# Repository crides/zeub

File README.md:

# Zeub

zeub is meant to be a pixel clock and a IoT hub. The name comes from a smooshed version of zeit (German for time) and hub.

It currently has:
- a 8x8 RGB LED matrix and a 32x8 white LED matrix
- 2 2-channel LED strip controllers (for controlling LED strips with warm and cool white lights in my room)
- a 128x64 OLED screen
- a TMP117 precision temperature sensor
- 2 front facing speakers, using 2 MAX98357 DACs
- a DS3212 battery backed RTC
- a EVQWGD001 rotary encoder, and a 5-way joystick
- a nRF52840 microcontroller, which supports USB, BLE and 802.15.4 (ZigBee etc.) protocols

Version 2 assembled displaying a clock icon and time (the right side is green because uh.. I messed up the PCBA parts assignment): 

The current firmware fetches the current time (once; supports connection at 2 times for drift correction) from a CTS (Current Time Service) from a BLE connection. This is currently done using my phone through the nRF Connect app. The time is then displayed on both the LED matrix (along with a clock icon), and the OLED along with the date and current temperature. It also sets the brightness of one LED strip using a preconfigured (but can be reconfigured through BLE) schedule. The other LED strip (which is actually my desk light) is controlled by the scroll wheel. It also streams audio from the USB to the speakers, for testing of the audio interface.

The hub part of the project still doesn't really exist yet, as I haven't had time to get to it.

Version 1 has basically the same features, but also included 2 microphones for testing. However the LED matrix did not work properly as I used 2 LED matrix controllers together in the same matrix.

The LED strips were also connected through a TRRS cable but without an actual connector, as I flipped the control polarity of the LED strips (they are common anode instead of common cathode).

Case iterations for v1 (the cone in the back is for better airflow to the temperature sensor, for more accurate reading of the environment):

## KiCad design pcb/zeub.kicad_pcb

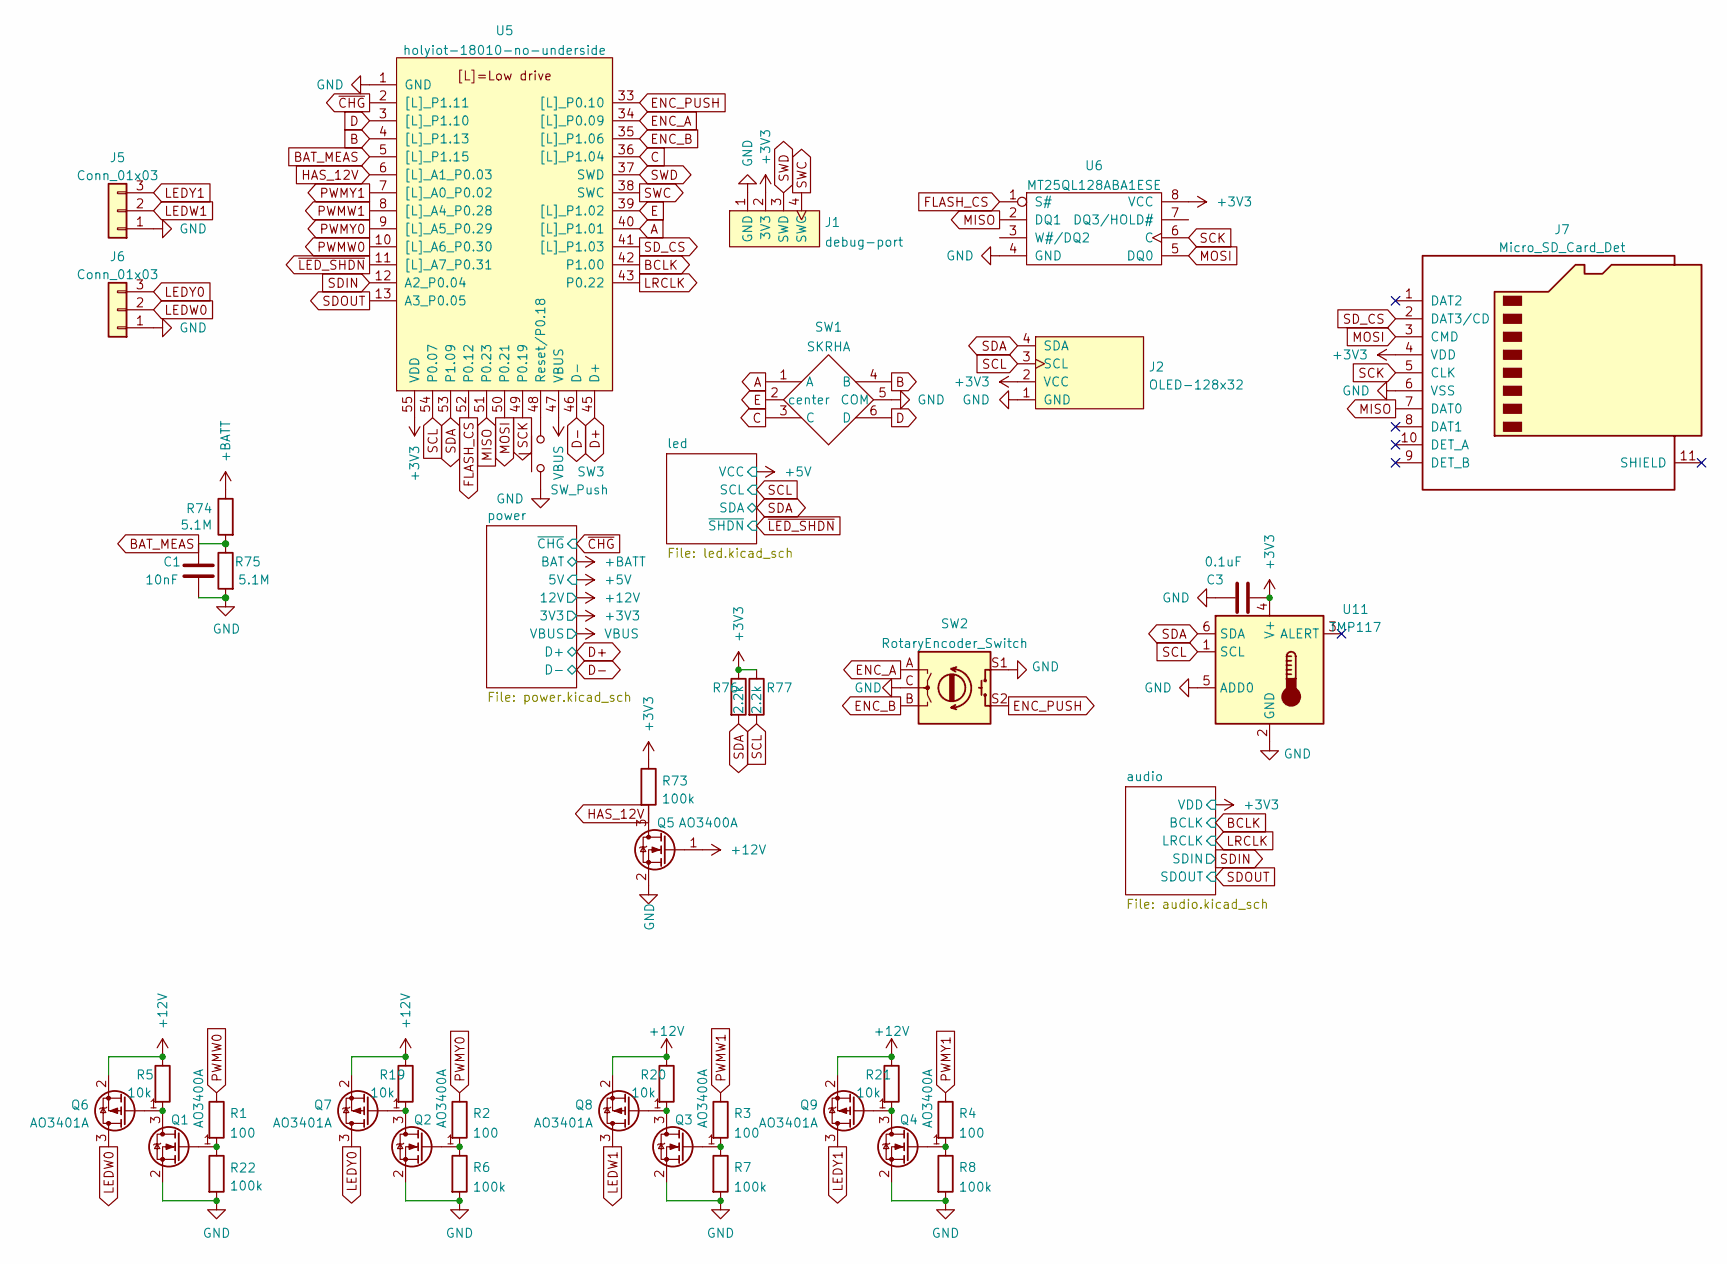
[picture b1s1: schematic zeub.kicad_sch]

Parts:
C1: 10nF; C_0603_1608Metric
C3: 0.1uF; C_0603_1608Metric
J1: debug-port; debug-port-single-side
J2: OLED-128x32; OLED-128x64
J5, J6: Conn_01x03; PinHeader_1x03_P2.54mm_Vertical
J7: Micro_SD_Card_Det; molex-503182-1852
Q1, Q2, Q3, Q4, Q5: AO3400A; SOT-23
Q6, Q7, Q8, Q9: AO3401A; SOT-23
R1, R2, R3, R4: 100; R_0603_1608Metric
R5, R19, R20, R21: 10k; R_0603_1608Metric
R6, R7, R8, R22, R73: 100k; R_0603_1608Metric
R74, R75: 5.1M; R_0603_1608Metric
R76, R77: 2.2k; R_0603_1608Metric
SW1: SKRHA; SKRHA-boss
SW2: RotaryEncoder_Switch; EVQWGD001
SW3: SW_Push; SW_SPST_B3U-1000P
U5: holyiot-18010-no-underside
U6: MT25QL128ABA1ESE; SOIC-8_5.23x5.23mm_P1.27mm
U11: TMP117; WSON-6-1EP_2x2mm_P0.65mm_EP1x1.6mm

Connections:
+3V3: C3.2, J1.2 (3V3), J2.2 (VCC), J7.4 (VDD), R73.1, R76.1, R77.1, U5.55 (VDD), U6.8 (VCC), U11.4 (V+); also elsewhere on the board
+12V: Q5.1 (G), Q6.2 (S), Q7.2 (S), Q8.2 (S), Q9.2 (S), R5.1, R19.1, R20.1, R21.1; also elsewhere on the board
+BATT: R74.1; also elsewhere on the board
A: SW1.1 (A), U5.40 ([L]_P1.01)
B: SW1.4 (B), U5.4 ([L]_P1.13)
BAT_MEAS: C1.1, R74.2, R75.1, U5.5 ([L]_P1.15)
BCLK: U5.42 (P1.00); also elsewhere on the board
C: SW1.3 (C), U5.36 ([L]_P1.04)
D: SW1.6 (D), U5.3 ([L]_P1.10)
D+: U5.45 (D+); also elsewhere on the board
D-: U5.46 (D-); also elsewhere on the board
E: SW1.2 (center), U5.39 ([L]_P1.02)
ENC_A: SW2.A, U5.34 ([L]_P0.09)
ENC_B: SW2.B, U5.35 ([L]_P1.06)
ENC_PUSH: SW2.S2, U5.33 ([L]_P0.10)
FLASH_CS: U5.52 (P0.12), U6.1 (S#)
GND: C1.2, C3.1, J1.1 (GND), J2.1 (GND), J5.1, J6.1, J7.6 (VSS), Q1.2 (S), Q2.2 (S), Q3.2 (S), Q4.2 (S), Q5.2 (S), R6.2, R7.2, R8.2, R22.2, R75.2, SW1.5 (COM), SW2.C, SW2.S1, SW3.1, U5.1 (GND), U5.32 (GND), U5.44 (GND), U6.4 (GND), U11.2 (GND), U11.5 (ADD0), U11.7 (GND); also elsewhere on the board
HAS_12V: Q5.3 (D), R73.2, U5.6 ([L]_A1_P0.03)
LEDW0: J6.2, Q6.3 (D)
LEDW1: J5.2, Q8.3 (D)
LEDY0: J6.3, Q7.3 (D)
LEDY1: J5.3, Q9.3 (D)
LRCLK: U5.43 (P0.22); also elsewhere on the board
MISO: J7.7 (DAT0), U5.51 (P0.23), U6.2 (DQ1)
MOSI: J7.3 (CMD), U5.50 (P0.21), U6.5 (DQ0)
unnamed: Q1.1 (G), R1.2, R22.1
unnamed: Q1.3 (D), Q6.1 (G), R5.2
unnamed: Q2.1 (G), R2.2, R6.1
unnamed: Q2.3 (D), Q7.1 (G), R19.2
unnamed: Q3.1 (G), R3.2, R7.1
unnamed: Q3.3 (D), Q8.1 (G), R20.2
unnamed: Q4.1 (G), R4.2, R8.1
unnamed: Q4.3 (D), Q9.1 (G), R21.2
unnamed: SW3.2, U5.48 (Reset/P0.18)
PWMW0: R1.1, U5.10 ([L]_A6_P0.30)
PWMW1: R3.1, U5.8 ([L]_A4_P0.28)
PWMY0: R2.1, U5.9 ([L]_A5_P0.29)
PWMY1: R4.1, U5.7 ([L]_A0_P0.02)
SCK: J7.5 (CLK), U5.49 (P0.19), U6.6 (C)
SCL: J2.3 (SCL), R77.2, U5.54 (P0.07), U11.1 (SCL); also elsewhere on the board
SDA: J2.4 (SDA), R76.2, U5.53 (P1.09), U11.6 (SDA); also elsewhere on the board
SDIN: U5.12 (A2_P0.04); also elsewhere on the board
SDOUT: U5.13 (A3_P0.05); also elsewhere on the board
SD_CS: J7.2 (DAT3/CD), U5.41 ([L]_P1.03)
SWC: J1.4 (SWC), U5.38 (SWC)
SWD: J1.3 (SWD), U5.37 (SWD)
VBUS: U5.47 (VBUS); also elsewhere on the board
~CHG: U5.2 ([L]_P1.11); also elsewhere on the board
~LED_SHDN: U5.11 ([L]_A7_P0.31); also elsewhere on the board

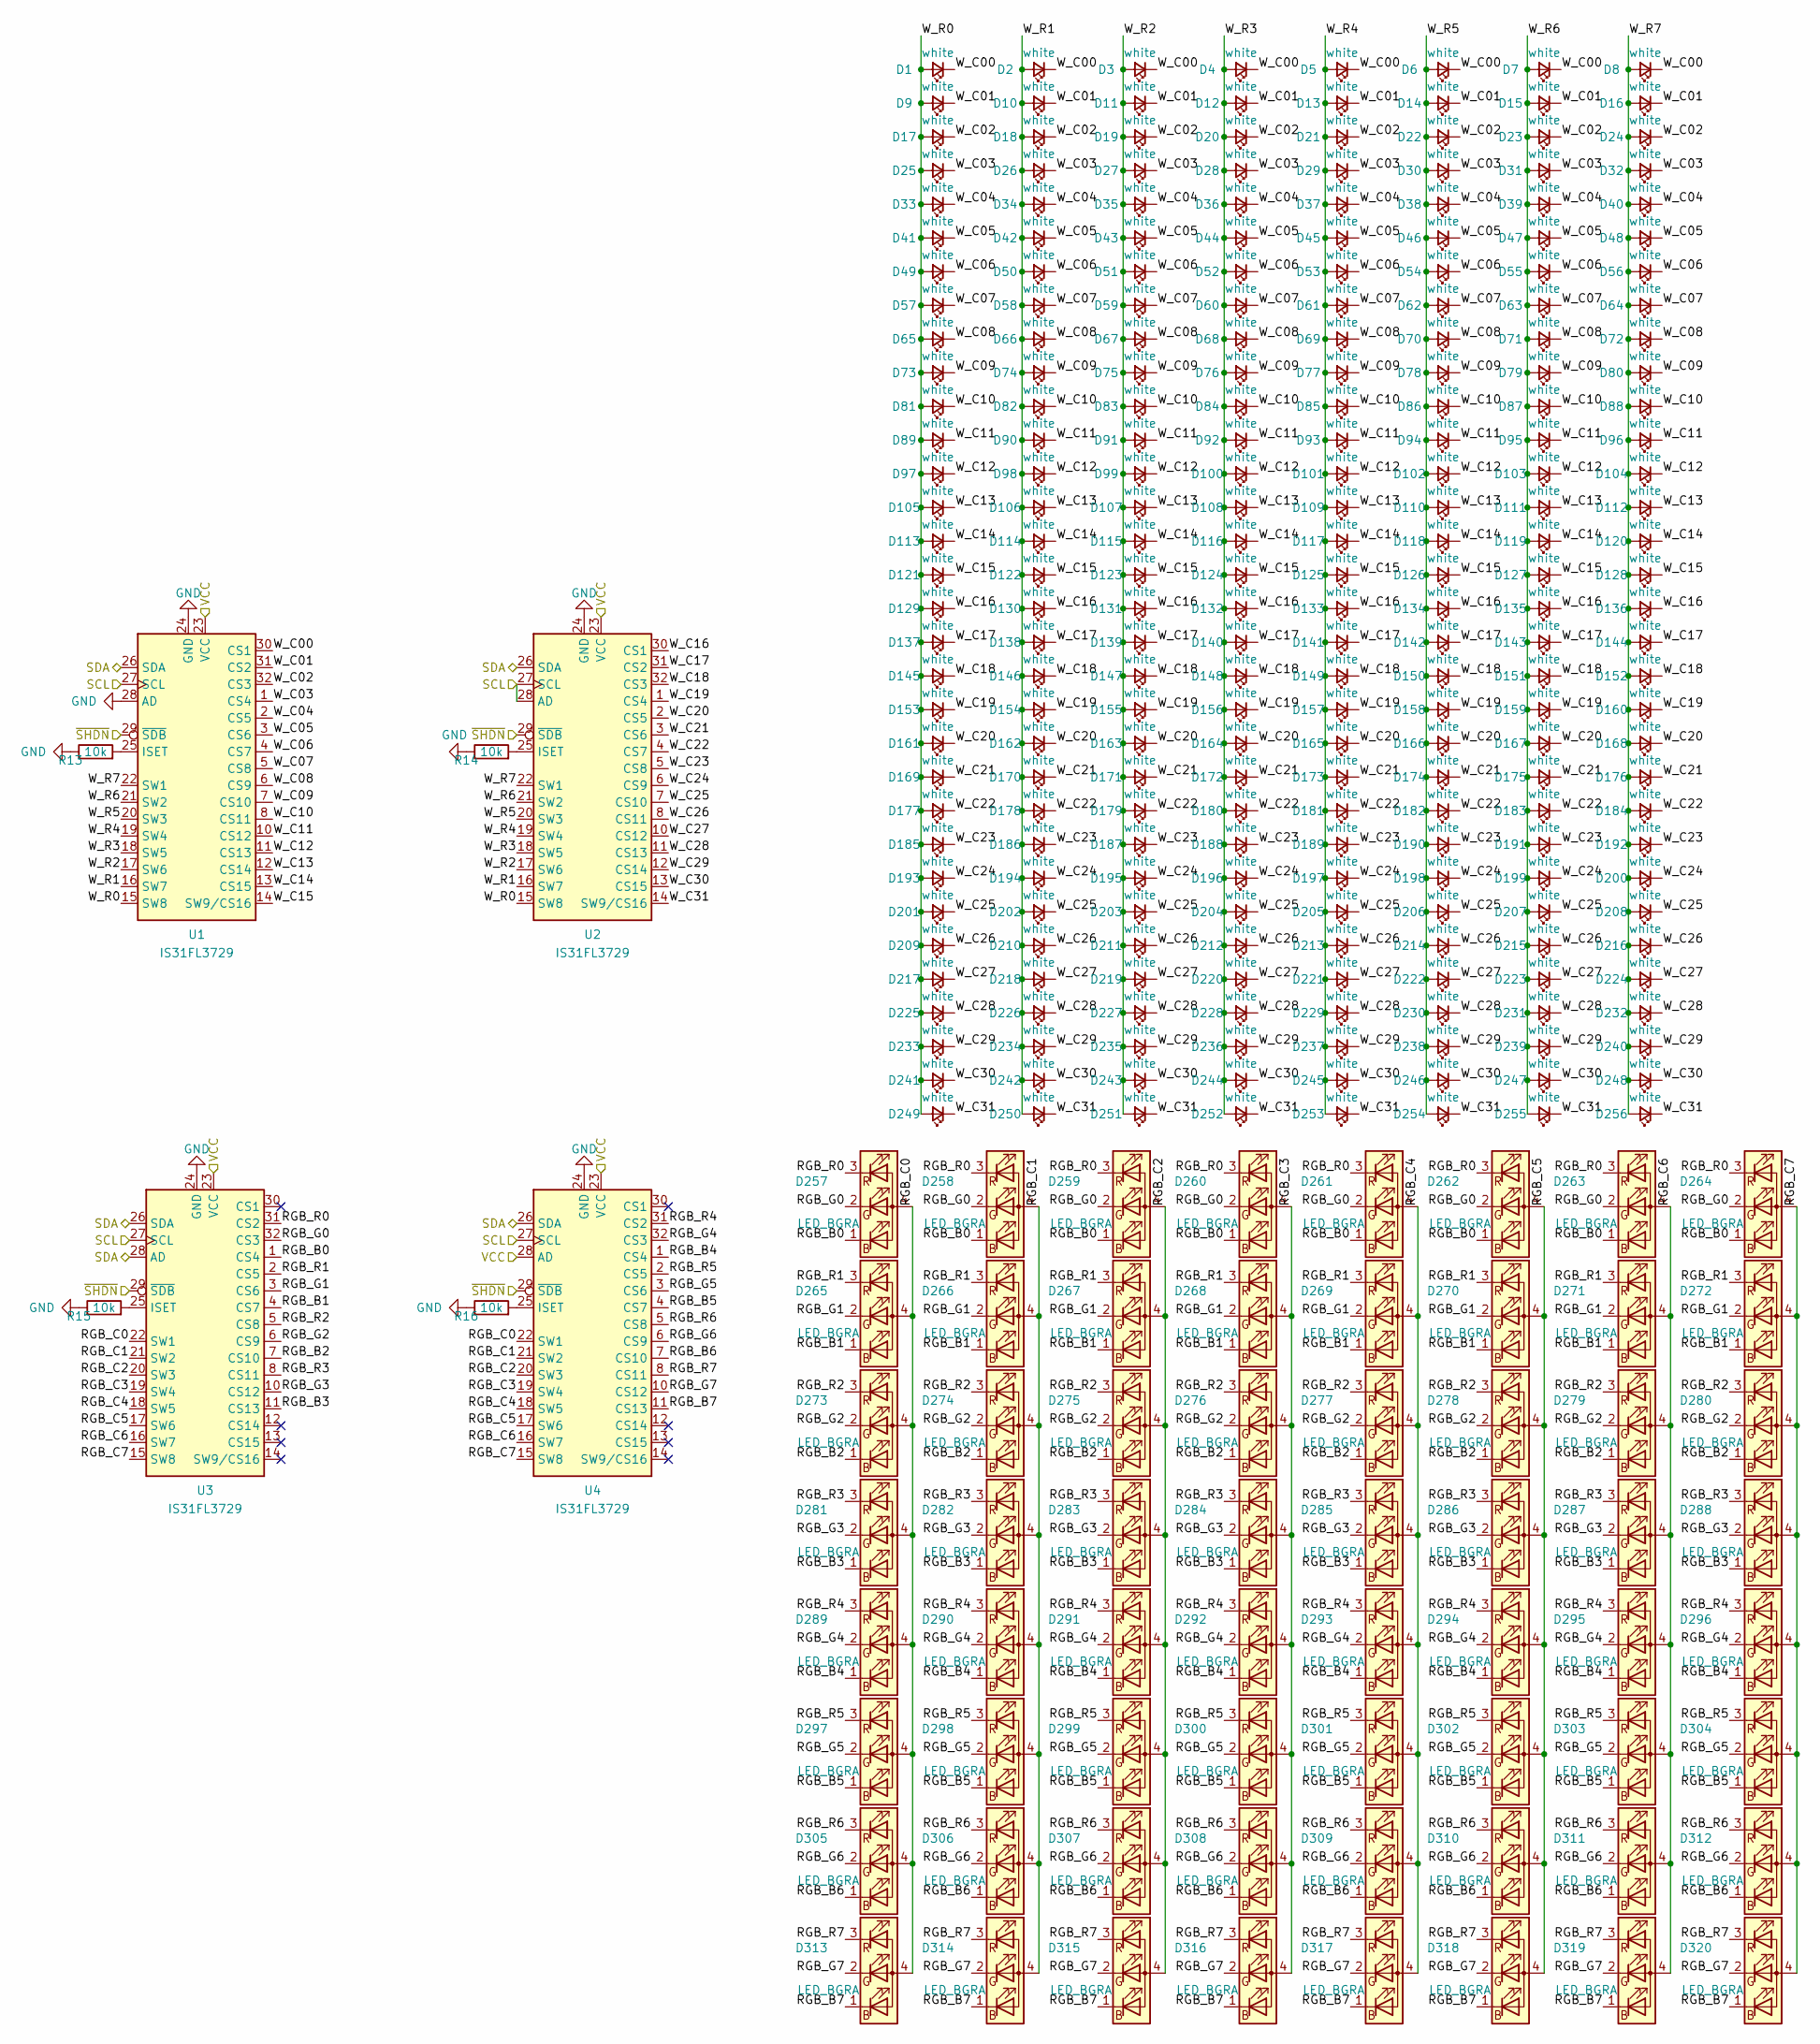
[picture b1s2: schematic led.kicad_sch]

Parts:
D1, D2, D3, D4, D5, D6, D7, D8, D9, D10, D11, D12, D13, D14, D15, D16, D17, D18, D19, D20, D21, D22, D23, D24, D25, D26, D27, D28, D29, D30, D31, D32, D33, D34, D35, D36, D37, D38, D39, D40, D41, D42, D43, D44, D45, D46, D47, D48, D49, D50, D51, D52, D53, D54, D55, D56, D57, D58, D59, D60, D61, D62, D63, D64, D65, D66, D67, D68, D69, D70, D71, D72, D73, D74, D75, D76, D77, D78, D79, D80, D81, D82, D83, D84, D85, D86, D87, D88, D89, D90, D91, D92, D93, D94, D95, D96, D97, D98, D99, D100, D101, D102, D103, D104, D105, D106, D107, D108, D109, D110, D111, D112, D113, D114, D115, D116, D117, D118, D119, D120, D121, D122, D123, D124, D125, D126, D127, D128, D129, D130, D131, D132, D133, D134, D135, D136, D137, D138, D139, D140, D141, D142, D143, D144, D145, D146, D147, D148, D149, D150, D151, D152, D153, D154, D155, D156, D157, D158, D159, D160, D161, D162, D163, D164, D165, D166, D167, D168, D169, D170, D171, D172, D173, D174, D175, D176, D177, D178, D179, D180, D181, D182, D183, D184, D185, D186, D187, D188, D189, D190, D191, D192, D193, D194, D195, D196, D197, D198, D199, D200, D201, D202, D203, D204, D205, D206, D207, D208, D209, D210, D211, D212, D213, D214, D215, D216, D217, D218, D219, D220, D221, D222, D223, D224, D225, D226, D227, D228, D229, D230, D231, D232, D233, D234, D235, D236, D237, D238, D239, D240, D241, D242, D243, D244, D245, D246, D247, D248, D249, D250, D251, D252, D253, D254, D255, D256: white; D_0603_1608Metric
D257, D258, D259, D260, D261, D262, D263, D264, D265, D266, D267, D268, D269, D270, D271, D272, D273, D274, D275, D276, D277, D278, D279, D280, D281, D282, D283, D284, D285, D286, D287, D288, D289, D290, D291, D292, D293, D294, D295, D296, D297, D298, D299, D300, D301, D302, D303, D304, D305, D306, D307, D308, D309, D310, D311, D312, D313, D314, D315, D316, D317, D318, D319, D320: LED_BGRA; LED_ASMB-KTF0-0A306
R13, R14, R15, R16: 10k; R_0603_1608Metric
U1, U2, U3, U4: IS31FL3729; eTQFP-32_7x7mm_P0.8mm

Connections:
+5V: U1.23 (VCC), U2.23 (VCC), U3.23 (VCC), U4.23 (VCC), U4.28 (AD); also elsewhere on the board
/led/RGB_B0: D257.1 (BK), D258.1 (BK), D259.1 (BK), D260.1 (BK), D261.1 (BK), D262.1 (BK), D263.1 (BK), D264.1 (BK), U3.1 (CS4)
/led/RGB_B1: D265.1 (BK), D266.1 (BK), D267.1 (BK), D268.1 (BK), D269.1 (BK), D270.1 (BK), D271.1 (BK), D272.1 (BK), U3.4 (CS7)
/led/RGB_B2: D273.1 (BK), D274.1 (BK), D275.1 (BK), D276.1 (BK), D277.1 (BK), D278.1 (BK), D279.1 (BK), D280.1 (BK), U3.7 (CS10)
/led/RGB_B3: D281.1 (BK), D282.1 (BK), D283.1 (BK), D284.1 (BK), D285.1 (BK), D286.1 (BK), D287.1 (BK), D288.1 (BK), U3.11 (CS13)
/led/RGB_B4: D289.1 (BK), D290.1 (BK), D291.1 (BK), D292.1 (BK), D293.1 (BK), D294.1 (BK), D295.1 (BK), D296.1 (BK), U4.1 (CS4)
/led/RGB_B5: D297.1 (BK), D298.1 (BK), D299.1 (BK), D300.1 (BK), D301.1 (BK), D302.1 (BK), D303.1 (BK), D304.1 (BK), U4.4 (CS7)
/led/RGB_B6: D305.1 (BK), D306.1 (BK), D307.1 (BK), D308.1 (BK), D309.1 (BK), D310.1 (BK), D311.1 (BK), D312.1 (BK), U4.7 (CS10)
/led/RGB_B7: D313.1 (BK), D314.1 (BK), D315.1 (BK), D316.1 (BK), D317.1 (BK), D318.1 (BK), D319.1 (BK), D320.1 (BK), U4.11 (CS13)
/led/RGB_C0: D257.4 (A), D265.4 (A), D273.4 (A), D281.4 (A), D289.4 (A), D297.4 (A), D305.4 (A), D313.4 (A), U3.22 (SW1), U4.22 (SW1)
/led/RGB_C1: D258.4 (A), D266.4 (A), D274.4 (A), D282.4 (A), D290.4 (A), D298.4 (A), D306.4 (A), D314.4 (A), U3.21 (SW2), U4.21 (SW2)
/led/RGB_C2: D259.4 (A), D267.4 (A), D275.4 (A), D283.4 (A), D291.4 (A), D299.4 (A), D307.4 (A), D315.4 (A), U3.20 (SW3), U4.20 (SW3)
/led/RGB_C3: D260.4 (A), D268.4 (A), D276.4 (A), D284.4 (A), D292.4 (A), D300.4 (A), D308.4 (A), D316.4 (A), U3.19 (SW4), U4.19 (SW4)
/led/RGB_C4: D261.4 (A), D269.4 (A), D277.4 (A), D285.4 (A), D293.4 (A), D301.4 (A), D309.4 (A), D317.4 (A), U3.18 (SW5), U4.18 (SW5)
/led/RGB_C5: D262.4 (A), D270.4 (A), D278.4 (A), D286.4 (A), D294.4 (A), D302.4 (A), D310.4 (A), D318.4 (A), U3.17 (SW6), U4.17 (SW6)
/led/RGB_C6: D263.4 (A), D271.4 (A), D279.4 (A), D287.4 (A), D295.4 (A), D303.4 (A), D311.4 (A), D319.4 (A), U3.16 (SW7), U4.16 (SW7)
/led/RGB_C7: D264.4 (A), D272.4 (A), D280.4 (A), D288.4 (A), D296.4 (A), D304.4 (A), D312.4 (A), D320.4 (A), U3.15 (SW8), U4.15 (SW8)
/led/RGB_G0: D257.2 (GK), D258.2 (GK), D259.2 (GK), D260.2 (GK), D261.2 (GK), D262.2 (GK), D263.2 (GK), D264.2 (GK), U3.32 (CS3)
/led/RGB_G1: D265.2 (GK), D266.2 (GK), D267.2 (GK), D268.2 (GK), D269.2 (GK), D270.2 (GK), D271.2 (GK), D272.2 (GK), U3.3 (CS6)
/led/RGB_G2: D273.2 (GK), D274.2 (GK), D275.2 (GK), D276.2 (GK), D277.2 (GK), D278.2 (GK), D279.2 (GK), D280.2 (GK), U3.6 (CS9)
/led/RGB_G3: D281.2 (GK), D282.2 (GK), D283.2 (GK), D284.2 (GK), D285.2 (GK), D286.2 (GK), D287.2 (GK), D288.2 (GK), U3.10 (CS12)
/led/RGB_G4: D289.2 (GK), D290.2 (GK), D291.2 (GK), D292.2 (GK), D293.2 (GK), D294.2 (GK), D295.2 (GK), D296.2 (GK), U4.32 (CS3)
/led/RGB_G5: D297.2 (GK), D298.2 (GK), D299.2 (GK), D300.2 (GK), D301.2 (GK), D302.2 (GK), D303.2 (GK), D304.2 (GK), U4.3 (CS6)
/led/RGB_G6: D305.2 (GK), D306.2 (GK), D307.2 (GK), D308.2 (GK), D309.2 (GK), D310.2 (GK), D311.2 (GK), D312.2 (GK), U4.6 (CS9)
/led/RGB_G7: D313.2 (GK), D314.2 (GK), D315.2 (GK), D316.2 (GK), D317.2 (GK), D318.2 (GK), D319.2 (GK), D320.2 (GK), U4.10 (CS12)
/led/RGB_R0: D257.3 (RK), D258.3 (RK), D259.3 (RK), D260.3 (RK), D261.3 (RK), D262.3 (RK), D263.3 (RK), D264.3 (RK), U3.31 (CS2)
/led/RGB_R1: D265.3 (RK), D266.3 (RK), D267.3 (RK), D268.3 (RK), D269.3 (RK), D270.3 (RK), D271.3 (RK), D272.3 (RK), U3.2 (CS5)
/led/RGB_R2: D273.3 (RK), D274.3 (RK), D275.3 (RK), D276.3 (RK), D277.3 (RK), D278.3 (RK), D279.3 (RK), D280.3 (RK), U3.5 (CS8)
/led/RGB_R3: D281.3 (RK), D282.3 (RK), D283.3 (RK), D284.3 (RK), D285.3 (RK), D286.3 (RK), D287.3 (RK), D288.3 (RK), U3.8 (CS11)
/led/RGB_R4: D289.3 (RK), D290.3 (RK), D291.3 (RK), D292.3 (RK), D293.3 (RK), D294.3 (RK), D295.3 (RK), D296.3 (RK), U4.31 (CS2)
/led/RGB_R5: D297.3 (RK), D298.3 (RK), D299.3 (RK), D300.3 (RK), D301.3 (RK), D302.3 (RK), D303.3 (RK), D304.3 (RK), U4.2 (CS5)
/led/RGB_R6: D305.3 (RK), D306.3 (RK), D307.3 (RK), D308.3 (RK), D309.3 (RK), D310.3 (RK), D311.3 (RK), D312.3 (RK), U4.5 (CS8)
/led/RGB_R7: D313.3 (RK), D314.3 (RK), D315.3 (RK), D316.3 (RK), D317.3 (RK), D318.3 (RK), D319.3 (RK), D320.3 (RK), U4.8 (CS11)
/led/W_C00: D1.1 (K), D2.1 (K), D3.1 (K), D4.1 (K), D5.1 (K), D6.1 (K), D7.1 (K), D8.1 (K), U1.30 (CS1)
/led/W_C01: D9.1 (K), D10.1 (K), D11.1 (K), D12.1 (K), D13.1 (K), D14.1 (K), D15.1 (K), D16.1 (K), U1.31 (CS2)
/led/W_C02: D17.1 (K), D18.1 (K), D19.1 (K), D20.1 (K), D21.1 (K), D22.1 (K), D23.1 (K), D24.1 (K), U1.32 (CS3)
/led/W_C03: D25.1 (K), D26.1 (K), D27.1 (K), D28.1 (K), D29.1 (K), D30.1 (K), D31.1 (K), D32.1 (K), U1.1 (CS4)
/led/W_C04: D33.1 (K), D34.1 (K), D35.1 (K), D36.1 (K), D37.1 (K), D38.1 (K), D39.1 (K), D40.1 (K), U1.2 (CS5)
/led/W_C05: D41.1 (K), D42.1 (K), D43.1 (K), D44.1 (K), D45.1 (K), D46.1 (K), D47.1 (K), D48.1 (K), U1.3 (CS6)
/led/W_C06: D49.1 (K), D50.1 (K), D51.1 (K), D52.1 (K), D53.1 (K), D54.1 (K), D55.1 (K), D56.1 (K), U1.4 (CS7)
/led/W_C07: D57.1 (K), D58.1 (K), D59.1 (K), D60.1 (K), D61.1 (K), D62.1 (K), D63.1 (K), D64.1 (K), U1.5 (CS8)
/led/W_C08: D65.1 (K), D66.1 (K), D67.1 (K), D68.1 (K), D69.1 (K), D70.1 (K), D71.1 (K), D72.1 (K), U1.6 (CS9)
/led/W_C09: D73.1 (K), D74.1 (K), D75.1 (K), D76.1 (K), D77.1 (K), D78.1 (K), D79.1 (K), D80.1 (K), U1.7 (CS10)
/led/W_C10: D81.1 (K), D82.1 (K), D83.1 (K), D84.1 (K), D85.1 (K), D86.1 (K), D87.1 (K), D88.1 (K), U1.8 (CS11)
/led/W_C11: D89.1 (K), D90.1 (K), D91.1 (K), D92.1 (K), D93.1 (K), D94.1 (K), D95.1 (K), D96.1 (K), U1.10 (CS12)
/led/W_C12: D97.1 (K), D98.1 (K), D99.1 (K), D100.1 (K), D101.1 (K), D102.1 (K), D103.1 (K), D104.1 (K), U1.11 (CS13)
/led/W_C13: D105.1 (K), D106.1 (K), D107.1 (K), D108.1 (K), D109.1 (K), D110.1 (K), D111.1 (K), D112.1 (K), U1.12 (CS14)
/led/W_C14: D113.1 (K), D114.1 (K), D115.1 (K), D116.1 (K), D117.1 (K), D118.1 (K), D119.1 (K), D120.1 (K), U1.13 (CS15)
/led/W_C15: D121.1 (K), D122.1 (K), D123.1 (K), D124.1 (K), D125.1 (K), D126.1 (K), D127.1 (K), D128.1 (K), U1.14 (SW9/CS16)
/led/W_C16: D129.1 (K), D130.1 (K), D131.1 (K), D132.1 (K), D133.1 (K), D134.1 (K), D135.1 (K), D136.1 (K), U2.30 (CS1)
/led/W_C17: D137.1 (K), D138.1 (K), D139.1 (K), D140.1 (K), D141.1 (K), D142.1 (K), D143.1 (K), D144.1 (K), U2.31 (CS2)
/led/W_C18: D145.1 (K), D146.1 (K), D147.1 (K), D148.1 (K), D149.1 (K), D150.1 (K), D151.1 (K), D152.1 (K), U2.32 (CS3)
/led/W_C19: D153.1 (K), D154.1 (K), D155.1 (K), D156.1 (K), D157.1 (K), D158.1 (K), D159.1 (K), D160.1 (K), U2.1 (CS4)
/led/W_C20: D161.1 (K), D162.1 (K), D163.1 (K), D164.1 (K), D165.1 (K), D166.1 (K), D167.1 (K), D168.1 (K), U2.2 (CS5)
/led/W_C21: D169.1 (K), D170.1 (K), D171.1 (K), D172.1 (K), D173.1 (K), D174.1 (K), D175.1 (K), D176.1 (K), U2.3 (CS6)
/led/W_C22: D177.1 (K), D178.1 (K), D179.1 (K), D180.1 (K), D181.1 (K), D182.1 (K), D183.1 (K), D184.1 (K), U2.4 (CS7)
/led/W_C23: D185.1 (K), D186.1 (K), D187.1 (K), D188.1 (K), D189.1 (K), D190.1 (K), D191.1 (K), D192.1 (K), U2.5 (CS8)
/led/W_C24: D193.1 (K), D194.1 (K), D195.1 (K), D196.1 (K), D197.1 (K), D198.1 (K), D199.1 (K), D200.1 (K), U2.6 (CS9)
/led/W_C25: D201.1 (K), D202.1 (K), D203.1 (K), D204.1 (K), D205.1 (K), D206.1 (K), D207.1 (K), D208.1 (K), U2.7 (CS10)
/led/W_C26: D209.1 (K), D210.1 (K), D211.1 (K), D212.1 (K), D213.1 (K), D214.1 (K), D215.1 (K), D216.1 (K), U2.8 (CS11)
/led/W_C27: D217.1 (K), D218.1 (K), D219.1 (K), D220.1 (K), D221.1 (K), D222.1 (K), D223.1 (K), D224.1 (K), U2.10 (CS12)
/led/W_C28: D225.1 (K), D226.1 (K), D227.1 (K), D228.1 (K), D229.1 (K), D230.1 (K), D231.1 (K), D232.1 (K), U2.11 (CS13)
/led/W_C29: D233.1 (K), D234.1 (K), D235.1 (K), D236.1 (K), D237.1 (K), D238.1 (K), D239.1 (K), D240.1 (K), U2.12 (CS14)
/led/W_C30: D241.1 (K), D242.1 (K), D243.1 (K), D244.1 (K), D245.1 (K), D246.1 (K), D247.1 (K), D248.1 (K), U2.13 (CS15)
/led/W_C31: D249.1 (K), D250.1 (K), D251.1 (K), D252.1 (K), D253.1 (K), D254.1 (K), D255.1 (K), D256.1 (K), U2.14 (SW9/CS16)
/led/W_R0: D1.2 (A), D9.2 (A), D17.2 (A), D25.2 (A), D33.2 (A), D41.2 (A), D49.2 (A), D57.2 (A), D65.2 (A), D73.2 (A), D81.2 (A), D89.2 (A), D97.2 (A), D105.2 (A), D113.2 (A), D121.2 (A), D129.2 (A), D137.2 (A), D145.2 (A), D153.2 (A), D161.2 (A), D169.2 (A), D177.2 (A), D185.2 (A), D193.2 (A), D201.2 (A), D209.2 (A), D217.2 (A), D225.2 (A), D233.2 (A), D241.2 (A), D249.2 (A), U1.15 (SW8), U2.15 (SW8)
/led/W_R1: D2.2 (A), D10.2 (A), D18.2 (A), D26.2 (A), D34.2 (A), D42.2 (A), D50.2 (A), D58.2 (A), D66.2 (A), D74.2 (A), D82.2 (A), D90.2 (A), D98.2 (A), D106.2 (A), D114.2 (A), D122.2 (A), D130.2 (A), D138.2 (A), D146.2 (A), D154.2 (A), D162.2 (A), D170.2 (A), D178.2 (A), D186.2 (A), D194.2 (A), D202.2 (A), D210.2 (A), D218.2 (A), D226.2 (A), D234.2 (A), D242.2 (A), D250.2 (A), U1.16 (SW7), U2.16 (SW7)
/led/W_R2: D3.2 (A), D11.2 (A), D19.2 (A), D27.2 (A), D35.2 (A), D43.2 (A), D51.2 (A), D59.2 (A), D67.2 (A), D75.2 (A), D83.2 (A), D91.2 (A), D99.2 (A), D107.2 (A), D115.2 (A), D123.2 (A), D131.2 (A), D139.2 (A), D147.2 (A), D155.2 (A), D163.2 (A), D171.2 (A), D179.2 (A), D187.2 (A), D195.2 (A), D203.2 (A), D211.2 (A), D219.2 (A), D227.2 (A), D235.2 (A), D243.2 (A), D251.2 (A), U1.17 (SW6), U2.17 (SW6)
/led/W_R3: D4.2 (A), D12.2 (A), D20.2 (A), D28.2 (A), D36.2 (A), D44.2 (A), D52.2 (A), D60.2 (A), D68.2 (A), D76.2 (A), D84.2 (A), D92.2 (A), D100.2 (A), D108.2 (A), D116.2 (A), D124.2 (A), D132.2 (A), D140.2 (A), D148.2 (A), D156.2 (A), D164.2 (A), D172.2 (A), D180.2 (A), D188.2 (A), D196.2 (A), D204.2 (A), D212.2 (A), D220.2 (A), D228.2 (A), D236.2 (A), D244.2 (A), D252.2 (A), U1.18 (SW5), U2.18 (SW5)
/led/W_R4: D5.2 (A), D13.2 (A), D21.2 (A), D29.2 (A), D37.2 (A), D45.2 (A), D53.2 (A), D61.2 (A), D69.2 (A), D77.2 (A), D85.2 (A), D93.2 (A), D101.2 (A), D109.2 (A), D117.2 (A), D125.2 (A), D133.2 (A), D141.2 (A), D149.2 (A), D157.2 (A), D165.2 (A), D173.2 (A), D181.2 (A), D189.2 (A), D197.2 (A), D205.2 (A), D213.2 (A), D221.2 (A), D229.2 (A), D237.2 (A), D245.2 (A), D253.2 (A), U1.19 (SW4), U2.19 (SW4)
/led/W_R5: D6.2 (A), D14.2 (A), D22.2 (A), D30.2 (A), D38.2 (A), D46.2 (A), D54.2 (A), D62.2 (A), D70.2 (A), D78.2 (A), D86.2 (A), D94.2 (A), D102.2 (A), D110.2 (A), D118.2 (A), D126.2 (A), D134.2 (A), D142.2 (A), D150.2 (A), D158.2 (A), D166.2 (A), D174.2 (A), D182.2 (A), D190.2 (A), D198.2 (A), D206.2 (A), D214.2 (A), D222.2 (A), D230.2 (A), D238.2 (A), D246.2 (A), D254.2 (A), U1.20 (SW3), U2.20 (SW3)
/led/W_R6: D7.2 (A), D15.2 (A), D23.2 (A), D31.2 (A), D39.2 (A), D47.2 (A), D55.2 (A), D63.2 (A), D71.2 (A), D79.2 (A), D87.2 (A), D95.2 (A), D103.2 (A), D111.2 (A), D119.2 (A), D127.2 (A), D135.2 (A), D143.2 (A), D151.2 (A), D159.2 (A), D167.2 (A), D175.2 (A), D183.2 (A), D191.2 (A), D199.2 (A), D207.2 (A), D215.2 (A), D223.2 (A), D231.2 (A), D239.2 (A), D247.2 (A), D255.2 (A), U1.21 (SW2), U2.21 (SW2)
/led/W_R7: D8.2 (A), D16.2 (A), D24.2 (A), D32.2 (A), D40.2 (A), D48.2 (A), D56.2 (A), D64.2 (A), D72.2 (A), D80.2 (A), D88.2 (A), D96.2 (A), D104.2 (A), D112.2 (A), D120.2 (A), D128.2 (A), D136.2 (A), D144.2 (A), D152.2 (A), D160.2 (A), D168.2 (A), D176.2 (A), D184.2 (A), D192.2 (A), D200.2 (A), D208.2 (A), D216.2 (A), D224.2 (A), D232.2 (A), D240.2 (A), D248.2 (A), D256.2 (A), U1.22 (SW1), U2.22 (SW1)
GND: R13.1, R14.1, R15.1, R16.1, U1.9 (GND), U1.24 (GND), U1.28 (AD), U1.33 (GND), U2.9 (GND), U2.24 (GND), U2.33 (GND), U3.9 (GND), U3.24 (GND), U3.33 (GND), U4.9 (GND), U4.24 (GND), U4.33 (GND); also elsewhere on the board
unnamed: R13.2, U1.25 (ISET)
unnamed: R14.2, U2.25 (ISET)
unnamed: R15.2, U3.25 (ISET)
unnamed: R16.2, U4.25 (ISET)
SCL: U1.27 (SCL), U2.27 (SCL), U2.28 (AD), U3.27 (SCL), U4.27 (SCL); also elsewhere on the board
SDA: U1.26 (SDA), U2.26 (SDA), U3.26 (SDA), U3.28 (AD), U4.26 (SDA); also elsewhere on the board
~LED_SHDN: U1.29 (~SDB), U2.29 (~SDB), U3.29 (~SDB), U4.29 (~SDB); also elsewhere on the board

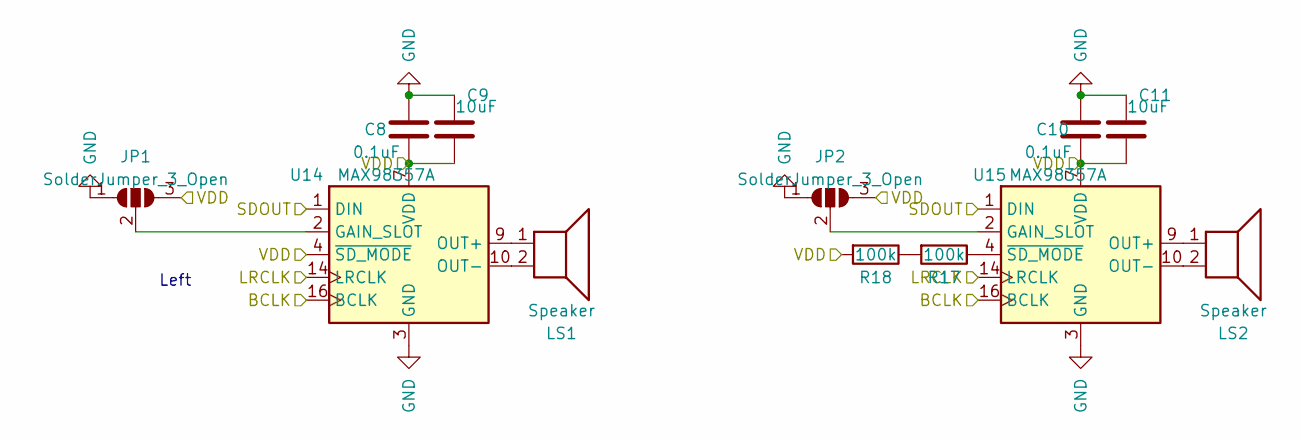
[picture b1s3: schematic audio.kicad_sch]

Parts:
C8, C10: 0.1uF; C_0603_1608Metric
C9, C11: 10uF; C_0603_1608Metric
JP1, JP2: SolderJumper_3_Open; SolderJumper-3_P1.3mm_Open_RoundedPad1.0x1.5mm
LS1, LS2: Speaker; CMS1609
R17, R18: 100k; R_0603_1608Metric
U14, U15: MAX98357A; QFN-16-1EP_3x3mm_P0.5mm_EP1.45x1.45mm

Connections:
+3V3: C8.2, C9.2, C10.2, C11.2, JP1.3 (B), JP2.3 (B), R18.2, U14.4 (~SD_MODE), U14.7 (VDD), U14.8 (VDD), U15.7 (VDD), U15.8 (VDD); also elsewhere on the board
BCLK: U14.16 (BCLK), U15.16 (BCLK); also elsewhere on the board
GND: C8.1, C9.1, C10.1, C11.1, JP1.1 (A), JP2.1 (A), U14.3 (GND), U14.11 (GND), U14.15 (GND), U14.17 (GND), U15.3 (GND), U15.11 (GND), U15.15 (GND), U15.17 (GND); also elsewhere on the board
LRCLK: U14.14 (LRCLK), U15.14 (LRCLK); also elsewhere on the board
unnamed: JP1.2 (C), U14.2 (GAIN_SLOT)
unnamed: JP2.2 (C), U15.2 (GAIN_SLOT)
unnamed: R17.1, U15.4 (~SD_MODE)
unnamed: R17.2, R18.1
SDOUT: U14.1 (DIN), U15.1 (DIN); also elsewhere on the board

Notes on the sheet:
Left

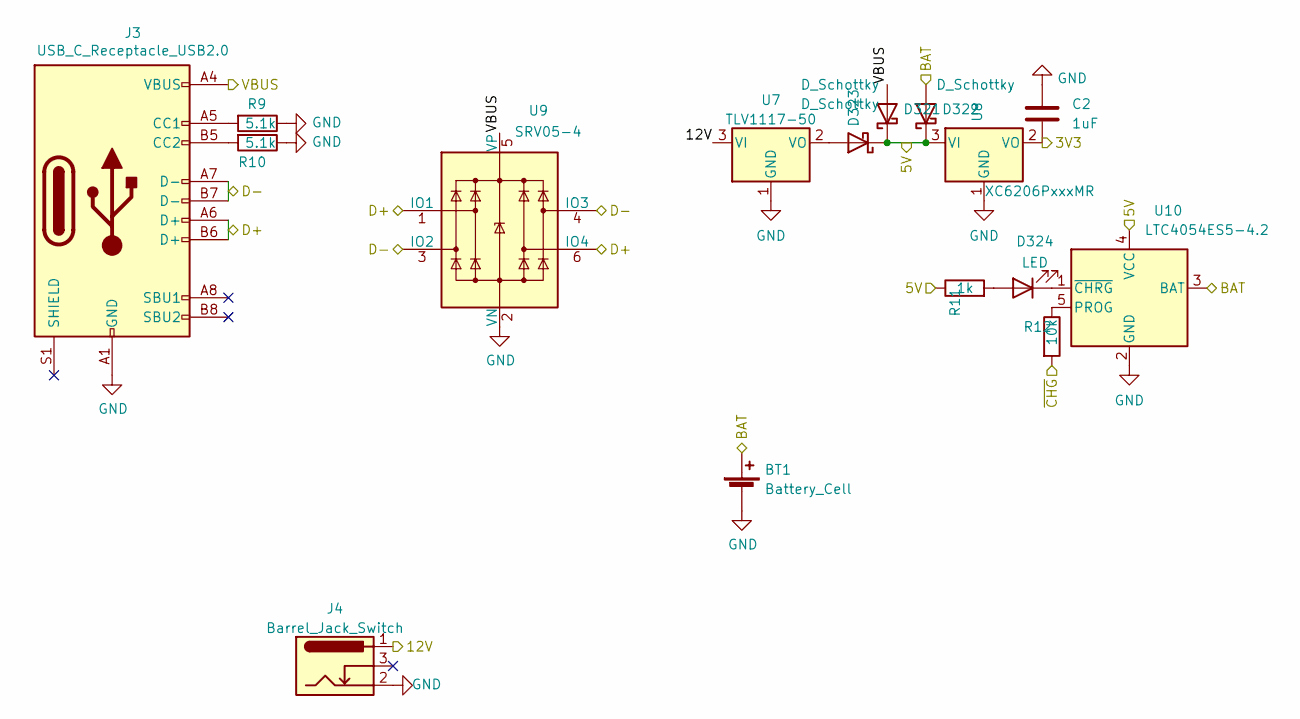
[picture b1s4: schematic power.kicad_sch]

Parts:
BT1: Battery_Cell; JST_PH_S2B-PH-SM4-TB_1x02-1MP_P2.00mm_Horizontal
C2: 1uF; C_0603_1608Metric
D321, D322, D323: D_Schottky; D_SOD-123
D324: LED; D_0805_2012Metric
J3: USB_C_Receptacle_USB2.0; USB_C_Receptacle_HRO_TYPE-C-31-M-12
J4: Barrel_Jack_Switch; BarrelJack_CUI_PJ-102AH_Horizontal
R9, R10: 5.1k; R_0603_1608Metric
R11: 1k; R_0603_1608Metric
R12: 10k; R_0603_1608Metric
U7: TLV1117-50; SOT-223
U8: XC6206PxxxMR; SOT-23
U9: SRV05-4; SOT-23-6
U10: LTC4054ES5-4.2; TSOT-23-5

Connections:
+3V3: C2.2, U8.2 (VO); also elsewhere on the board
+5V: D321.1 (K), D322.1 (K), D323.1 (K), R11.1, U8.3 (VI), U10.4 (VCC); also elsewhere on the board
+12V: J4.1, U7.3 (VI); also elsewhere on the board
+BATT: BT1.1 (+), D322.2 (A), U10.3 (BAT); also elsewhere on the board
D+: J3.A6 (D+), J3.B6 (D+), U9.1 (IO1), U9.6 (IO4); also elsewhere on the board
D-: J3.A7 (D-), J3.B7 (D-), U9.3 (IO2), U9.4 (IO3); also elsewhere on the board
GND: BT1.2 (-), C2.1, J3.A1 (GND), J3.A12 (GND), J3.B1 (GND), J3.B12 (GND), J4.2, R9.1, R10.1, U7.1 (GND), U8.1 (GND), U9.2 (VN), U10.2 (GND); also elsewhere on the board
unnamed: D323.2 (A), U7.2 (VO)
unnamed: D324.1 (K), U10.1 (~CHRG)
unnamed: D324.2 (A), R11.2
unnamed: J3.A5 (CC1), R9.2
unnamed: J3.B5 (CC2), R10.2
unnamed: R12.1, U10.5 (PROG)
VBUS: D321.2 (A), J3.A4 (VBUS), J3.A9 (VBUS), J3.B4 (VBUS), J3.B9 (VBUS), U9.5 (VP); also elsewhere on the board
~CHG: R12.2; also elsewhere on the board

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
